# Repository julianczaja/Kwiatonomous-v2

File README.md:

# Kwiatonomous-v2 

##### Kwiatonomous is a device for automatic plant watering. ESP8266 based, battery powered (super low power), own backend (in Ktor) and Android app (with Jetpack Compose).

___

### Android App

___

### Hardware
#### v0.5 (306070 Li-Po)

<details>
  <summary>v0.4 (Li-ion 18650)</summary>
  
</details>

___

### CAD
#### Case for v0.5 PCB

___

<p align="center">
🔥 More comming soon 🔥
</p>

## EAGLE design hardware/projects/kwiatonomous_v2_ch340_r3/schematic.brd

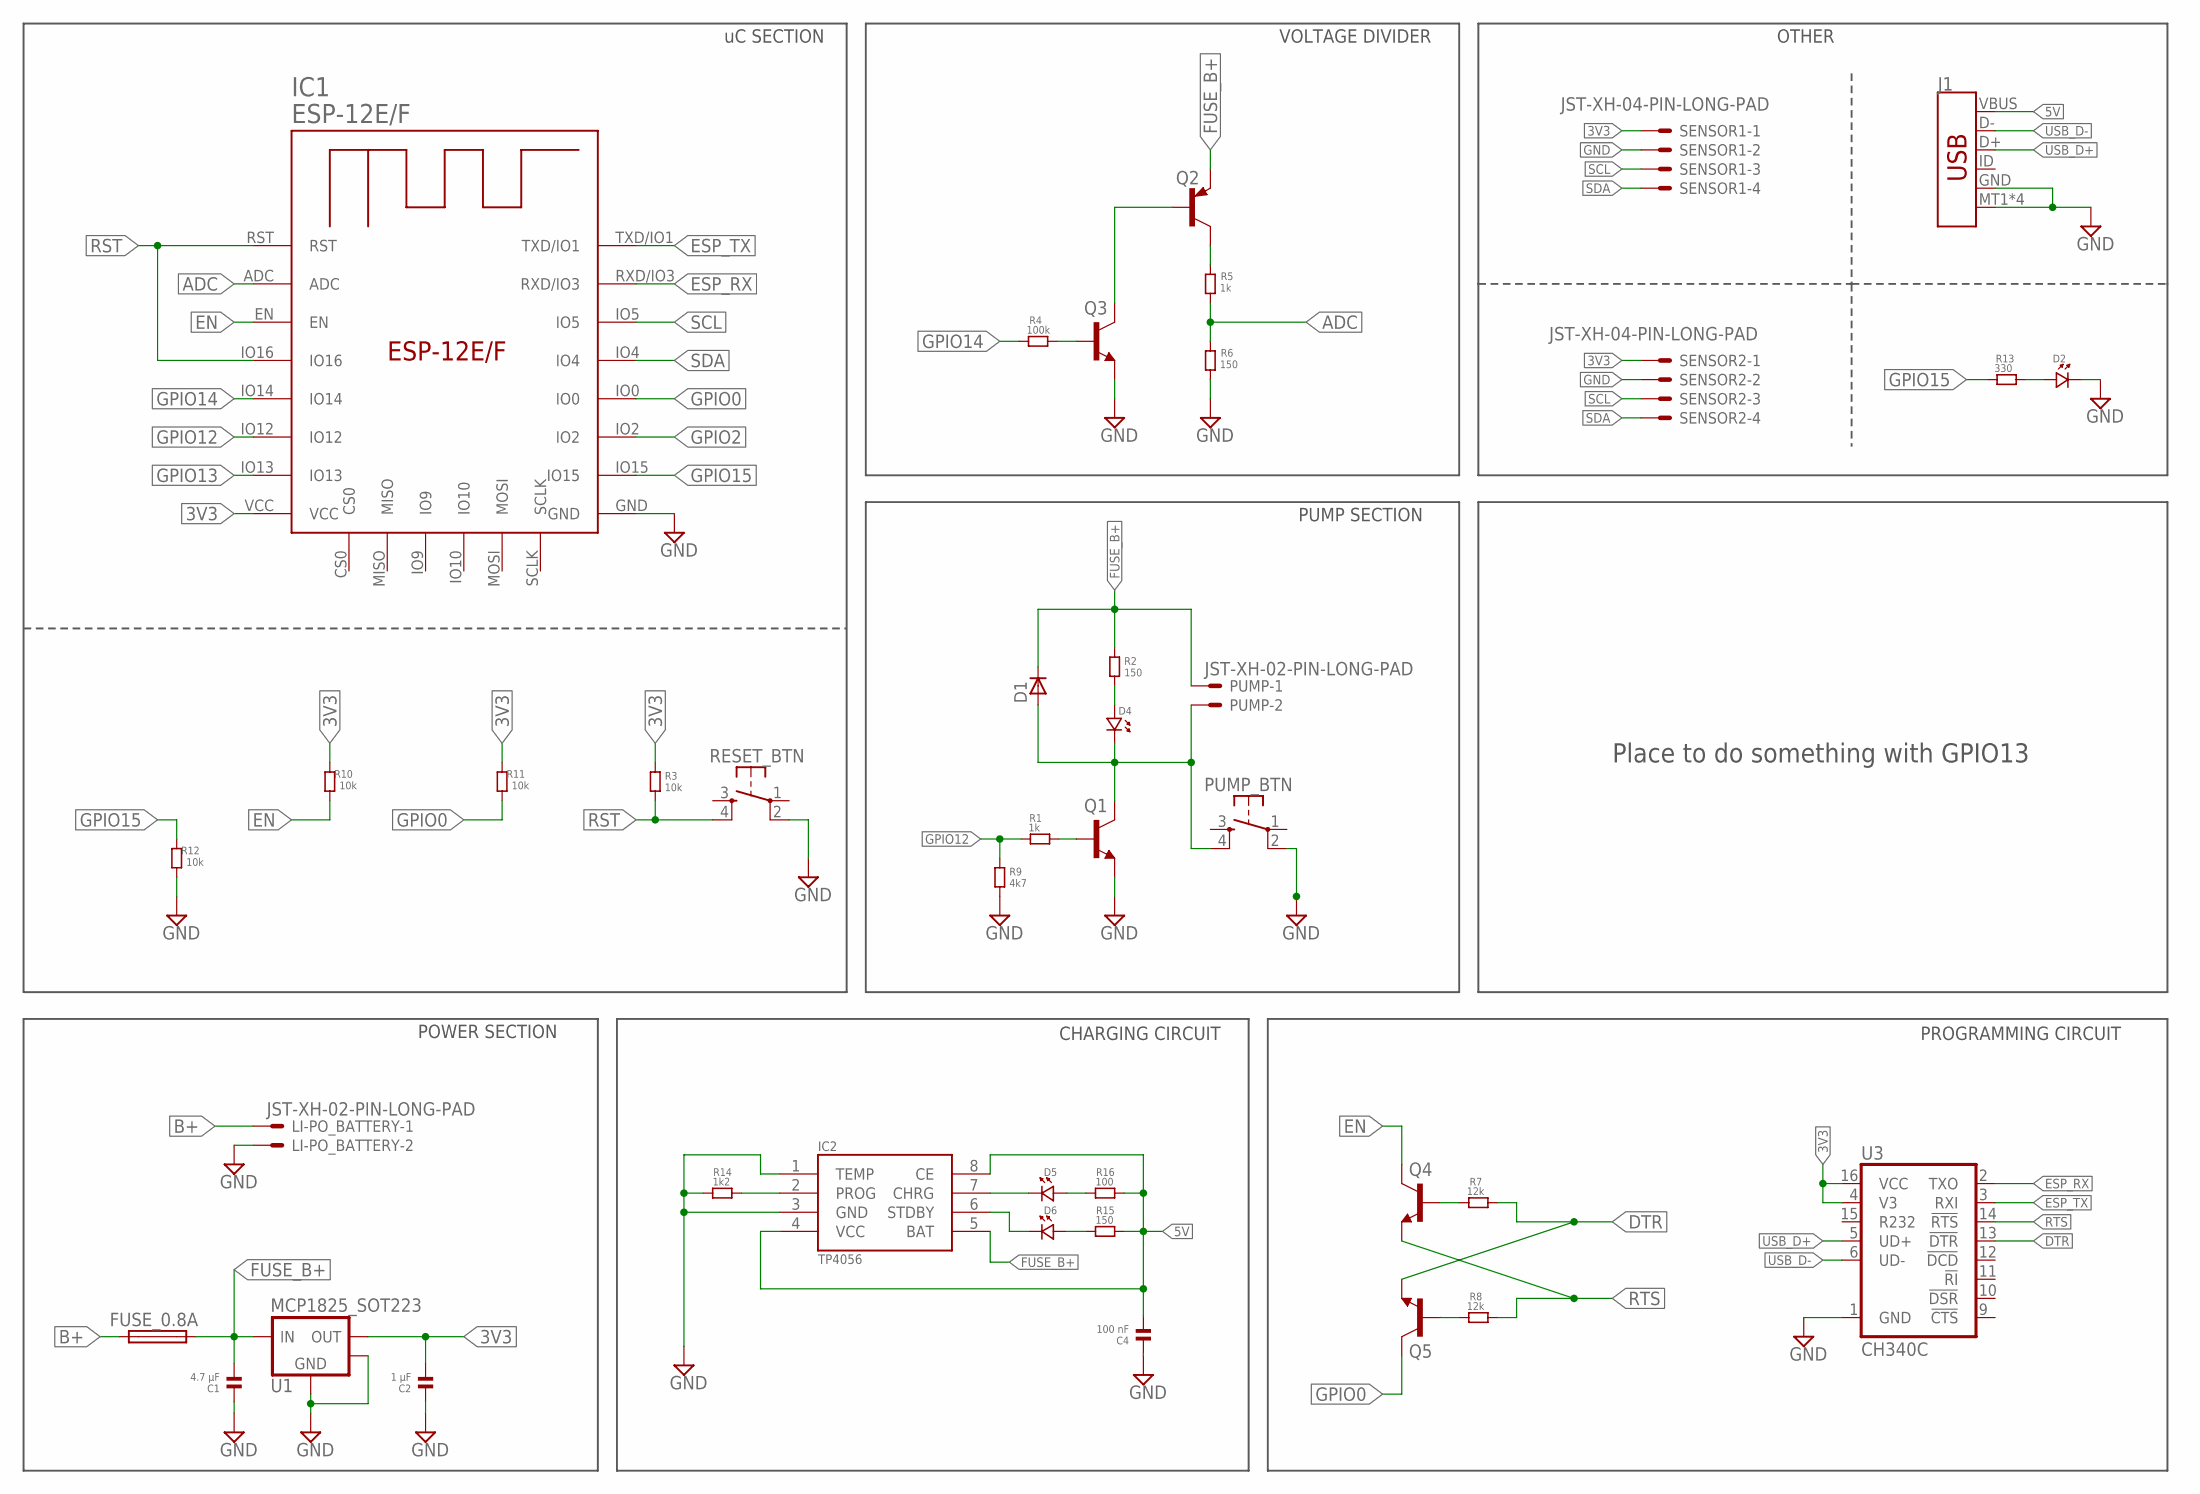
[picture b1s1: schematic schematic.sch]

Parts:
C1: 4.7 μF; 1206
C2: 1 μF; 1206
C4: 100 nF; 1206
D1: 1N4148WS; SOD323F
D2, D4, D5, D6: LED.1206; 1206.LED
FUSE_0.8A: FUSE_KWIATONOMOUS; SHK20L
IC1: ESP-12E/F; ESP-12E
IC2: TP4056; SOP-8
J1: USB_MICRO-B_SMT; USB-MICROB
LI-PO_BATTERY: JST-XH-02-PIN-LONG-PAD; JST-XH-02-PACKAGE-LONG-PAD
PUMP: JST-XH-02-PIN-LONG-PAD; JST-XH-02-PACKAGE-LONG-PAD
PUMP_BTN: DTSM-6
Q1, Q3, Q4, Q5: BCW71SMD; SOT23-BEC
Q2: BCX71SMD; SOT23
R1, R5: 1k; 1206
R2, R6, R15: 150; 1206
R3, R10, R11, R12: 10k; 1206
R4: 100k; 1206
R7, R8: 12k; 1206
R9: 4k7; 1206
R13: 330; 1206
R14: 1k2; 1206
R16: 100; 1206
RESET_BTN: DTSM-6
SENSOR1, SENSOR2: JST-XH-04-PIN-LONG-PAD; JST-XH-04-PACKAGE-LONG-PAD
U1: MCP1825_SOT223; SOT-223-3
U3: CH340C; SO016

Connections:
3V3: C2.2, IC1.VCC, R3.1, R10.1, R11.1, SENSOR1.1, SENSOR2.1, U1.3 (VOUT), U3.4 (V3), U3.16 (VCC)
5V: C4.2, IC2.4 (VCC), IC2.8 (CE), J1.VBUS, R15.2, R16.2
ADC: IC1.ADC, R5.2, R6.1
B+: FUSE_0.8A.1A (1), FUSE_0.8A.1B (1), LI-PO_BATTERY.1
DTR: Q5.E, R7.2, U3.13 (!DTR)
EN: IC1.EN, Q4.C, R10.2
ESP_RX: IC1.RXD/IO3, U3.2 (TXO)
ESP_TX: IC1.TXD/IO1, U3.3 (RXI)
FUSE_B+: C1.2, D1.C, FUSE_0.8A.2A (2), FUSE_0.8A.2B (2), IC2.5 (BAT), PUMP.1, Q2.2 (E), R2.1, U1.1 (VIN)
GND: C1.1, C2.1, C4.1, D2.P$2 (2), IC1.GND, IC2.1 (TEMP), IC2.3 (GND), J1.GND, J1.MT1 (SHIELD), J1.MT2 (SHIELD), J1.P$1 (SHIELD), J1.P$2 (SHIELD), LI-PO_BATTERY.2, PUMP_BTN.2, Q1.E, Q3.E, R6.2, R9.2, R12.2, R14.1, RESET_BTN.2, SENSOR1.2, SENSOR2.2, U1.2 (GND), U1.4 (HEATSINK), U3.1 (GND)
GPIO0: IC1.IO0, Q5.C, R11.2
GPIO2: IC1.IO2
GPIO12: IC1.IO12, R1.1, R9.1
GPIO13: IC1.IO13
GPIO14: IC1.IO14, R4.1
GPIO15: IC1.IO15, R12.1, R13.1
unnamed: Q1.B, R1.2
unnamed: Q3.B, R4.2
unnamed: D4.P$1 (1), R2.2
unnamed: D1.A, D4.P$2 (2), PUMP.2, PUMP_BTN.4, Q1.C
unnamed: Q2.3 (C), R5.1
unnamed: Q5.B, R8.1
unnamed: Q4.B, R7.1
unnamed: D2.P$1 (1), R13.2
unnamed: IC2.2 (PROG), R14.2
unnamed: D5.P$2 (2), IC2.7 (CHRG)
unnamed: D6.P$1 (1), R15.1
unnamed: D5.P$1 (1), R16.1
unnamed: D6.P$2 (2), IC2.6 (STDBY)
PG: Q2.1 (B), Q3.C
RST: IC1.IO16, IC1.RST, R3.2, RESET_BTN.4
RTS: Q4.E, R8.2, U3.14 (!RTS)
SCL: IC1.IO5, SENSOR1.3, SENSOR2.3
SDA: IC1.IO4, SENSOR1.4, SENSOR2.4
USB_D+: J1.D+, U3.5 (UD+)
USB_D-: J1.D-, U3.6 (UD-)

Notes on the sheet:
POWER SECTION
PROGRAMMING CIRCUIT
OTHER
uC SECTION
PUMP SECTION
VOLTAGE DIVIDER
CHARGING CIRCUIT
Place to do something with GPIO13

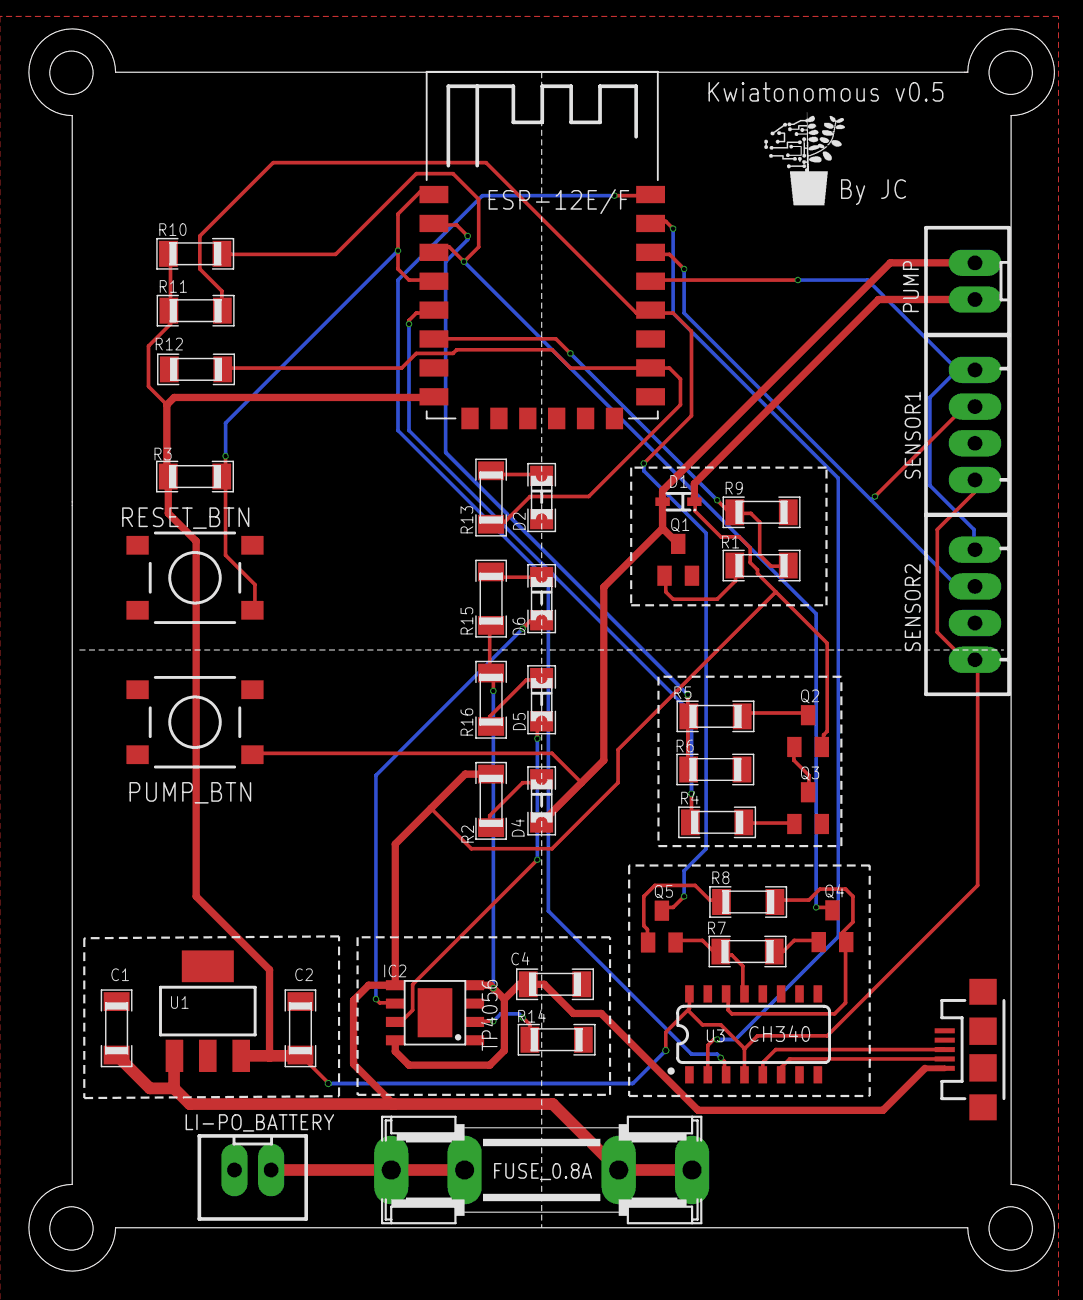
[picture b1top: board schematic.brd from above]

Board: 2 copper layers, 71.0 x 86.0 mm, 41 parts (0 on the bottom side), 34 nets.

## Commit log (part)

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2021-10-20 Added backend files
2021-10-20 Added Eagle files
2021-10-20 Added cad files
2021-10-20 Added esp8266 project files
2021-10-20 Implemened test code for esp8266
2021-10-28 embedded/Improved test code
2021-10-28 android/Initial commit
2021-10-28 android/Added dependencies to project
2021-10-30 android/Implemented application skeleton, DI and API
2021-10-30 android/Started dashboard screen implementation
2021-10-30 backend/Refactored DeviceUpdate class
2021-10-30 android/Implemented DeviceUpdate API calls
2021-10-30 backend/Improved DB calls
2021-11-07 android/Added navigation and device updates. UI improvements.
2021-11-08 android/Added basic splash screen
2021-11-15 embedded/Improved battery manager. Code cleanup.
2021-11-15 embedded/Improved sleeping intervals and errors handling
2021-11-24 android/Improved line chart. Added preview.
2021-11-28 backend/Added nextWatering to DeviceUpdate class
2021-11-28 backend/Implemented device configuration table and improved next watering
2021-11-30 embedded/Implemented device configuration and watering
2021-11-30 android/Added nextWatering to Device. Improved DeviceItem composable.
2021-11-30 embeded/Changed http client timeout to 3000ms
2021-12-05 backend/Removed nextWatering from DeviceUpdate. Added wateringTime to DeviceConfiguration
2021-12-05 embedded/Adjusted data to new changes in backend. Added next watering time updating.
2021-12-12 android/Added device settings
2021-12-18 backend/Added picking device updates from/to timestamp
2021-12-22 android/Added better charts with data based on given date.
2021-12-22 android/Refactored dashboard
2021-12-28 android/Dependencies update
2021-12-28 android/Added unit tests for DeviceConfiguration usecases
2021-12-28 android/Added unit tests for DeviceUpdate usecases
2021-12-28 android/Fixed UpdateDeviceConfigurationUseCase test
2021-12-28 backend/Improved error handing and debugging
2021-12-29 android/Moved DashboardScreen stuff to DeviceDetailsScreen. Implemented basic menu in dashboard.
2021-12-29 android/Added application settings skeleton
2022-01-04 embedded/Added data manger to handle EEPROM reads/writes. Code cleanup.
2022-01-05 embedded/Improved error handling
2022-01-05 embedded/Added KwiatonomousApi class
2022-01-07 backend/Switched from Netty to Jetty engine. Gradle dependencies update.
2022-01-07 embedded/Implemented watering times based on hardcoded values
2022-01-07 embedded/Added more logs
2022-01-07 embedded/Fixed watering manager bug with device start after long shutdown
2022-01-09 backend/Added default values as constants
2022-01-09 android/Implemented device time zone offset
2022-01-09 embedded/Implemented time zones handing
2022-01-09 android/Improved charts
2022-01-10 android/Added device active state indicator
2022-01-10 android/Improved 'update' usecases to emit flow
2022-01-10 android/Fixed tests
2022-01-12 backend/Migrated from H2 to sqlite database
2022-01-13 backend/Unified naming
2022-01-13 android/Fixed device configuration conversion
2022-01-16 android/Improved preloading cached data. Improved error handling
2022-01-19 android/Added screenshot
2022-01-23 android/UI improvements
2022-01-24 android/Minor UI improvements
2022-01-25 android/Fixed bugs when db is empty
2022-01-25 android/Fixed problem with automatic dark mode on Xiaomi devices
2022-01-28 android/Gradle update
2022-01-30 android/Implemented DevicesViewModel unit tests
2022-01-30 android/Implemented DeviceDetailsViewModel unit tests
2022-01-30 android/Added code style config
2022-01-30 android/Updated gitignore
2022-01-30 android/Replaced hardcoded strings
2022-01-30 android/Refactored chart type selection for better translation possibility
2022-01-30 android/Added polish strings
2022-01-30 android/Refactored DeviceItem to work better with polish language
2022-02-01 android/Set 'day' as default chart type in device details screen. Fixed string typo
2022-02-01 backend/Improved response codes
2022-02-03 android/Added user_device table to database and set up UserDeviceRepository
2022-02-03 android/Improved error boxes
2022-02-03 android/Refactored DevicesScreen to show UserDevices
2022-02-08 android/Refactored DAOs
    - Implemented 'addOrUpdate' function in DeviceDao, DeviceUpdateDao, DeviceConfigurationDao
    - Refactored use cases to use addOrUpdate
    - Changed naming
2022-02-10 backend/Fixed get device updates route to return empty list instead of 404
2022-02-14 android/Upgraded gradle version
2022-02-14 android/Refactored device details screen
    - Added UserDevice section
    - Moved DeviceItem and changet its UI
2022-02-16 android/Updated gradle dependencies
2022-02-16 android/Removed unnecessary job from DevicesViewModel
2022-02-16 android/Fixed and updated tests
2022-02-16 android/Updated readme
2022-02-19 android/Improved typography, code cleanup
2022-02-19 android/Added confirmation dialog when deleting user device
2022-03-14 hardware/Added new board revision files
2022-05-10 android/Added NetworkPreferences. Started to implement basic digest auth
2022-05-10 android/Added last update info to device view
2022-05-15 android/Added Glance widget skeleton
2022-05-15 android/Improved getting last devices updates
2022-05-17 android/Added battery level to device item
2022-05-19 android/Added nullOnEmptyConverterFactory
2022-05-19 android/Implemented KwiatonomousAppState
2022-05-19 android/Implemented simple register screen
2022-05-19 android/Partially implemented logging out
2022-05-21 android/Implemented User class. Cleaned up AuthManager a bit.
2022-05-25 android/Added exceptions handing in splash screen
2022-05-27 backend/Switched kotlinx-json to gson
2022-05-27 backend/Implemented digest authentication
    - Added User table
    - Refactored all routes
    - Created separate routes for ESP devices
2022-05-27 embedded/Adjusted configuration format
2022-05-27 android/Fixed unit tests
2022-05-31 android/Implemented ExpandableCardWithLabel
2022-05-31 android/Added content size animation to UserDeviceItem
2022-06-12 android/Updated libraries and Kotlin. Added Timber for logging
2022-06-23 android/Improved line charts
    - moved some constants to DateLineChartProperties
    - added enter animations
    - cleaned up code and packages
2022-06-23 android/Implemented chart settings
2022-06-27 android/Implemented device updates table view
2022-06-27 android/Turned off release build signing
2022-06-28 android/Implemented basic work manager setup (WIP)
2022-06-28 android/Upgraded dependencies and gradle version
2022-06-28 android/Disabled device updates table button when list is empty
2022-07-05 android/Addded app icon
2022-07-05 backend/Added field `notificationsOn` to UserDevice
2022-07-05 android/Added notification on/off setting to UserDevice
    - Extracted content of AddEditUserDeviceScreen for preview
    - Added notifications toggle in AddEditUserDeviceScreenContent
    - Added notifications toggle icon in DeviceDetailsScreen
    - Moved AppSettingsToggleItem to common components
2022-07-05 android/Added app notifications settings
2022-07-27 android/Added NotificationsManager, code cleanup
2022-07-27 android/Updated gitignore, uploaded old (v3) db scheme
2022-07-27 android/Adjusted font in DeviceItem and DeviceConfigurationItem
2022-07-27 backend/Added simple status website via FreeMaker. Version bumped to 0.0.9
2022-08-08 android/Implemented events
    - Added event models (DeviceEvent + entity and dto)
    - Added event enpoints to KwiatonomousApi
    - Added new database entity
    - Added device event repository
    - Added basic composable to display events
2022-08-09 android/Upgraded dependencies
2022-08-12 android/Implemented adding device events
    - ExpandableFloatingActionButton is used to choose what event user wants to add
    - Added AddDeviceEventUseCase
    - Added simple dialogs for UserNote and Watering events
    - Events UI improvements - new icons
    - minor fixes with scaffold's padding (because of compose 1.2.0)
2022-08-22 android/Implemented adding device low battery events
2022-08-22 backend/Implemented events
    - added new table to database
    - added routes for Android
2022-08-22 backend/Added 'userName' column do User table
2022-08-22 android/Changed UserDevice's image from drawable id to name
2022-08-22 backend/Changed UserDevice's deviceImageId to deviceImageName
2022-08-22 embedded/Implemented sending watering event
2022-08-22 backend/Added method for esp to send events
2022-08-23 android/Refactored getDeviceEvents to get all user's devices' events
2022-08-24 android/Bumped gradle dependencies
2022-08-24 android/Improved login and register screens
    - password is now hidden
    - added simple validation for username, login and password
    - focus is changing of enter click
    - extracted login screen content for preview
2022-08-24 android/Added button to remove devices cache
    - refactored app settings screen for better preview
    - implemented ClearDevicesCacheUseCase
    - added removeAll() function to all repositories
    -
2022-08-24 android/Dashboard improvements
    - fixed bug with multiple same events
    - extracted DashboardScreen content for better preview
2022-08-25 android/Implemented hiding fab on scroll in DeviceDetailsScreen
2022-08-25 android/Implemented setting notifications time
    - refactored TimePicker a bit
    - added LocalTime converter for gson
    - created KwiatonomousWorkManager class
2022-08-25 android/Fixed tests. Added tests for getMinutesUntilLocalTime
2022-08-26 android/Implemented removing device events
2022-10-30 android/Refactored DashboardViewModel to have single uiState
2022-10-30 android/Added obfuscation to release build. Code cleanup
2022-10-31 android/Implemented devices widget
2022-10-31 android/String update
2022-11-15 backend/Added pump cleaning, updated dependencies, bumped version
2022-11-15 android/Added pump cleaning event and reminder
    - added KwiatonomousBroadcastReceiver
    - added lastPumpCleaning to Device
    - added notifications testing buttons in settings
    - added PumpCleaningWorker
    - added pump cleaning event
    - refactored BatteryBatteryInfoWorker
2022-11-15 android/Improved events UI
2022-11-17 android/Code cleanup in DeviceSettings VM and screen
2022-11-21 android/Devices and device details screens refactor. Dependencies bump
    - replaced accompanist swipe-refresh with compose one
    - added caching to GetUserDevicesWithLastUpdatesUseCase
    - switched from State to StateFlow in view models
2022-11-21 android/Fixed bug in DeviceUpdateRepositoryImpl
    - limit param was not passed to DAO function
2022-11-21 android/Refactored LoginScreenViewModel to use StateFlow
2022-11-21 android/Refactored RegisterScreenViewModel to use StateFlow
2022-11-21 android/Fixed bug with not updated uiState when user don't have devices added
2022-11-22 android/Removed unused "lastUpdated" fields from Device and DeviceConfiguration tables
2022-11-22 android/Fixed release build
2022-11-22 android/Improved cancellable flows
2022-11-24 android/Improved dashboard screen
    - uiStateStream has now single source of truth (db)
    - fixed bug with flow being emitted too many times
    - code cleanup
2023-01-07 hardware/Added v0.5 version of PCB
    - replaced 18650 with Li-Po
    - added button for manual pump powering
    - new design
2023-01-30 embedded/Minor changes
    - updated AHT library to 2.0.3
    - adjusted LEDs sequences
    - adjusted WiFi settings to extend range
    - Code cleanup
2023-02-10 android/Bumped dependencies
    - Upgraded gradle to 8.0-rc-2
    - Upgraded java to 11
    - Upgraded kotlin to 1.8.10
    - bumped libs' versions
2023-02-10 android/Improved developer settings
2023-02-10 android/Fixed preloading old data on devices screen
2023-02-10 android/Implemented horizontal mode for dashboard screen
2023-02-10 android/Added hotfix for snackbars not disappearing when changing screens
2023-02-10 cad/Added case files for v0.5 PCB
2023-03-29 android/(kind of) fixed notifications in android 13
2023-08-22 android/Bumped dependencies and changed server url
2023-08-22 android/Fixed proguard rules
2023-08-22 embedded/Updated server url
2024-11-23 backend/Updated dependencies. Version 2.0
2024-11-23 android/Migrated to versions catalog
2024-12-01 backend/Minor fixes, code cleanup. Version 2.1
2024-12-01 android/Refactored devices widget

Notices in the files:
README.md:
License: MIT
parts and their libraries:
SparkFun-IC-Comms: Licensing: Creative Commons ShareAlike 4.0 International - https://creativecommons.org/licenses/by-sa/4.0
